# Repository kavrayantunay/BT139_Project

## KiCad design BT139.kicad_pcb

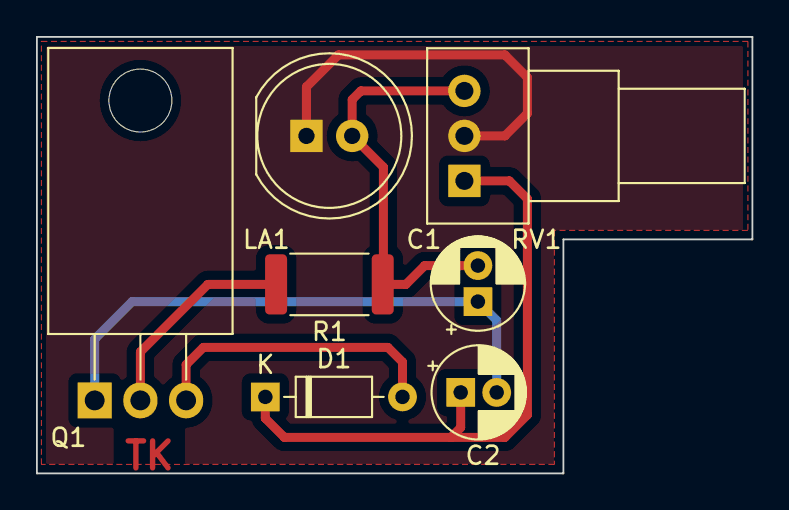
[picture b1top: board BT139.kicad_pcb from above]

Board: 2 copper layers, 39.8 x 24.2 mm, 7 parts (0 on the bottom side), 6 nets.

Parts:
C1: 10nF; CP_Radial_D5.0mm_P2.00mm
C2: 100nF; CP_Radial_D5.0mm_P2.00mm
D1: DB3; D_DO-35_SOD27_P7.62mm_Horizontal
LA1: Lamp; LED_D8.0mm
Q1: BT139-600; TO-220-3_Horizontal_TabDown
R1: 3.9k; R_2512_6332Metric
RV1: R_Potentiometer; Potentiometer_Alps_RK09Y11_Single_Horizontal

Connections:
GND: LA1.1 (-), RV1.2
unnamed: C1.1, C2.2, Q1.1 (A1)
unnamed: C1.2, LA1.2 (+), R1.1, RV1.3
unnamed: C2.1, D1.1 (K), RV1.1
unnamed: D1.2 (A), Q1.3 (G)
unnamed: Q1.2 (A2), R1.2
